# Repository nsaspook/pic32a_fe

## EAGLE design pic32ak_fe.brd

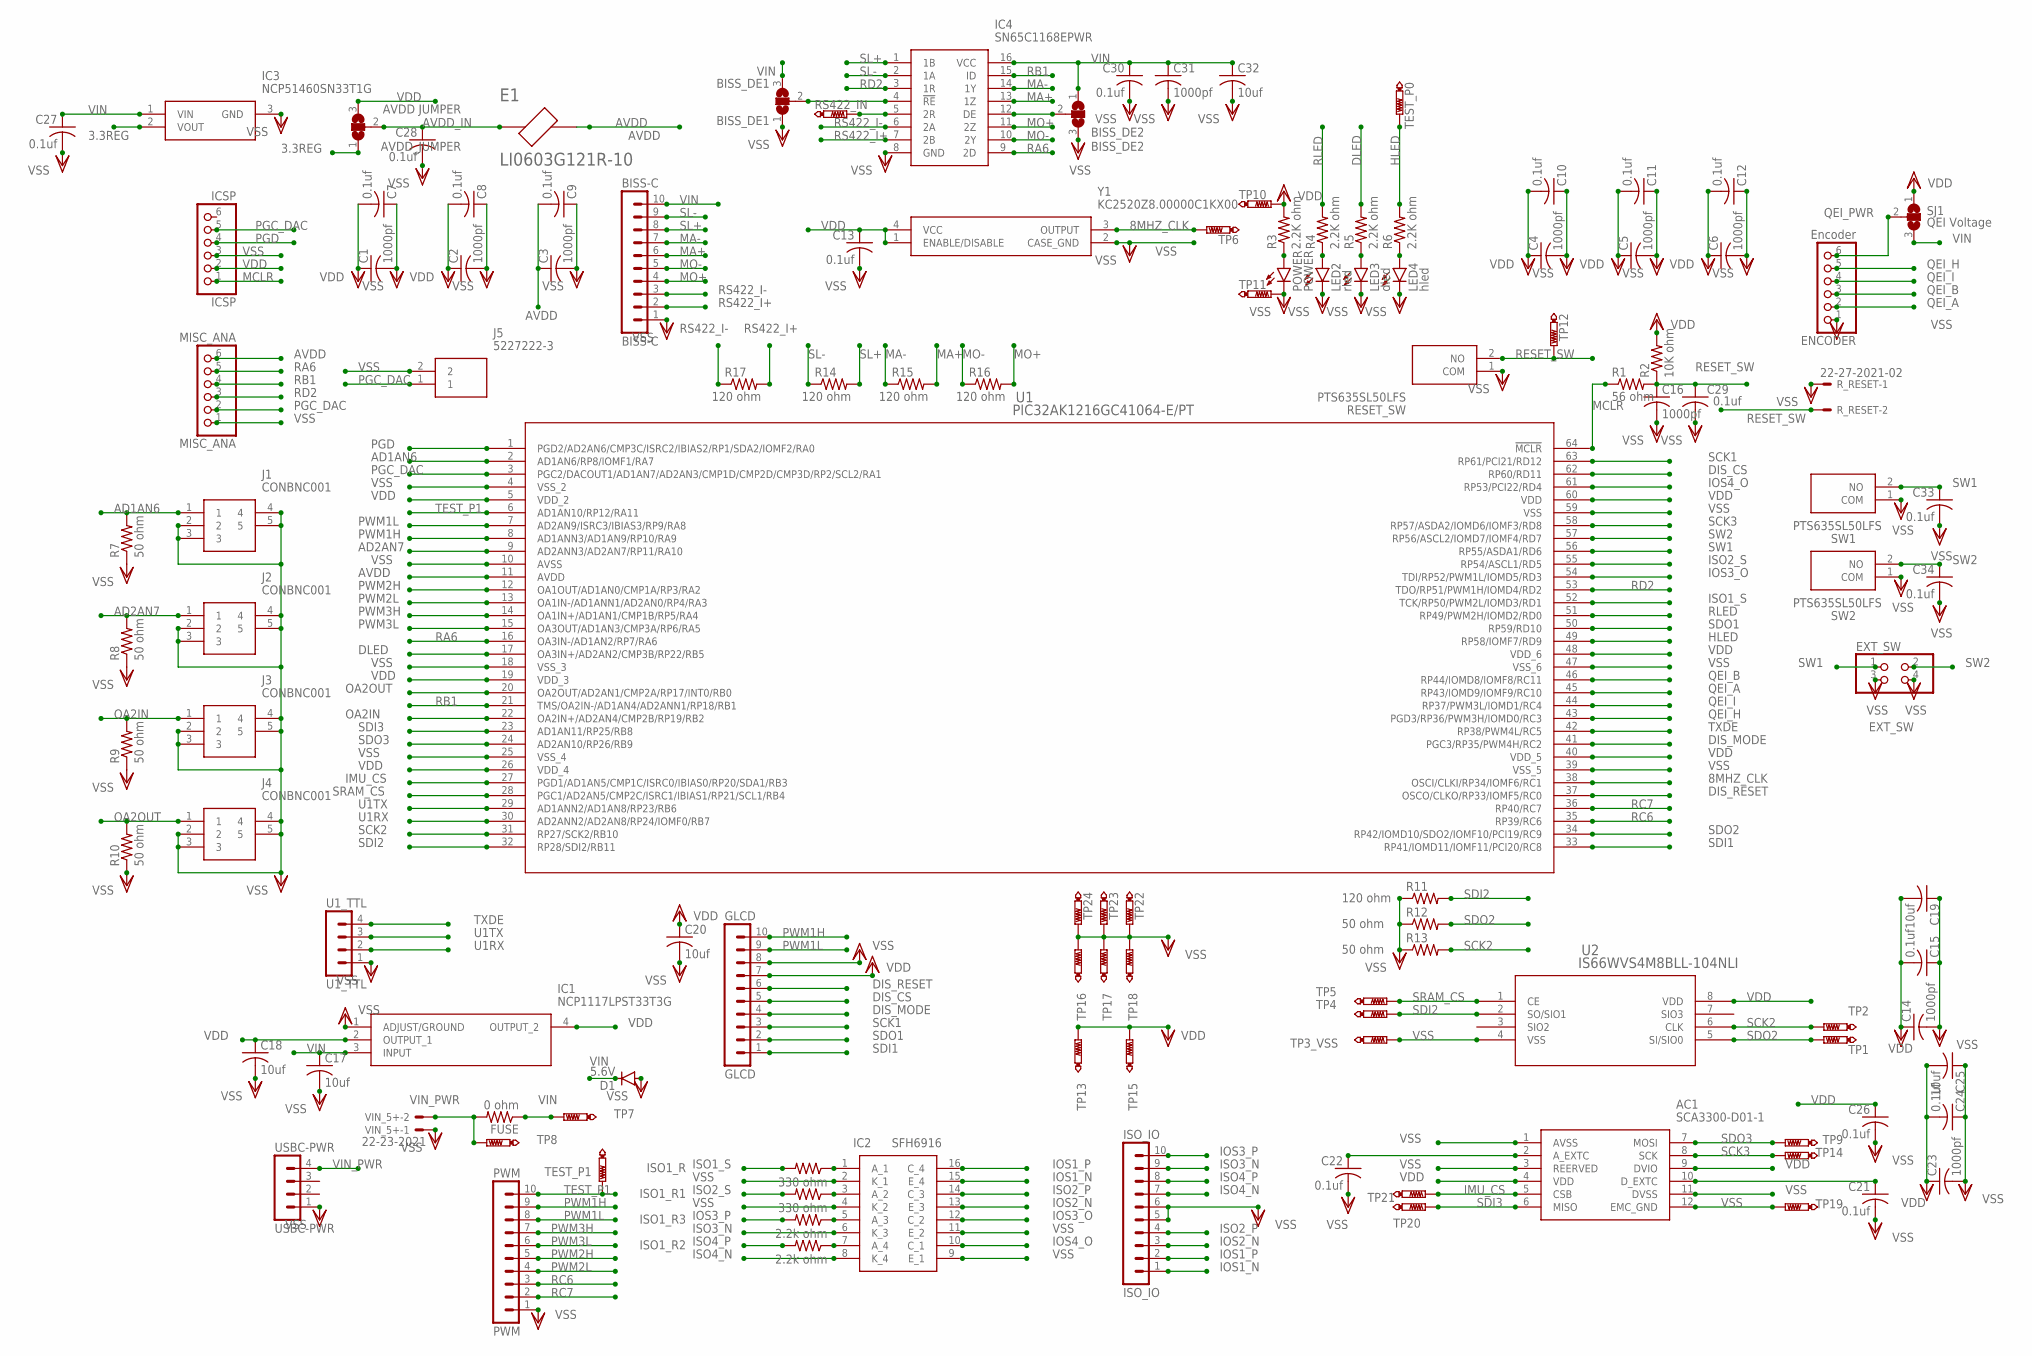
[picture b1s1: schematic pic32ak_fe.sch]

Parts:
AC1: SCA3300-D01-1; SCA3300
AVDD_JUMPER: AVDD JUMPER; SJ_2
BISS-C: BISS-C; MA10-1
BISS_DE1: BISS_DE1; SJ_2
BISS_DE2: BISS_DE2; SJ_2
C1, C2, C3, C4, C5, C6, C14, C16, C23, C31: 1000pf; C0603
C7, C8, C9, C10, C11, C12, C13, C15, C21, C22, C24, C26, C27, C28, C29, C30, C33, C34: 0.1uf; C0603
C17, C18, C19, C20, C25, C32: 10uf; C0805
D1: 5.6V; SMB
E1: LI0603G121R-10; FB_LI0603G121R-10
ENCODER: Encoder; 1X06/90
EXT_SW: EXT_SW; 2X02
FUSE: 0 ohm; R0805
GLCD: GLCD; MA10-1
IC1: NCP1117LPST33T3G; SOT230P700X180-4N
IC2: SFH6916; SOIC127P700X230-16N
IC3: NCP51460SN33T1G; SOT96P237X111-3N
IC4: SN65C1168EPWR; SOP65P640X120-16N
ICSP: ICSP; 1X06/90
ISO1_R, ISO1_R1: 330 ohm; R0805
ISO1_R2, ISO1_R3: 2.2k ohm; R0805
ISO_IO: ISO_IO; MA10-1
J1, J2, J3, J4: CONBNC001
J5: 5227222-3; 52272223
LED2: rled; CHIP-LED0603
LED3: dled; CHIP-LED0603
LED4: hled; CHIP-LED0603
MISC_ANA: MISC_ANA; 1X06/90
POWER: POWER; CHIP-LED0603
PWM: PWM; MA10-1
R1: 56 ohm; R0805
R2: 10K ohm; R0805
R3, R4, R5, R6: 2.2K ohm; R0805
R7, R8, R9, R10: 50 ohm; R0805
R11, R14, R15, R16, R17: 120 ohm; R0603
R12, R13: 50 ohm; R0603
RESET_SW: PTS635SL50LFS
RS422_IN: PTR1PAD1-13; P1-13
R_RESET: 22-27-2021-02; 6410-02
SJ1: QEI Voltage; SJ_2
SW1, SW2: PTS635SL50LFS
TEST_P0, TEST_P1: PTR1PAD1-20; P1-20
TP1, TP2, TP3_VSS, TP4, TP5, TP6, TP7, TP8, TP9, TP13, TP14, TP15, TP16, TP17, TP18, TP19, TP20, TP21, TP22, TP23, TP24: PTR1PAD1-13; P1-13
TP10, TP11, TP12: PTR1PAD1-20; P1-20
U1: PIC32AK1216GC41064-E/PT; TQFP64_PT_MCH
U1_TTL: U1_TTL; MA04-1
U2: IS66WVS4M8BLL-104NLI; SOIC8_150MIL_N_ISI
USBC-PWR: USBC-PWR; MA04-1
VIN_5+: 22-23-2021
Y1: KC2520Z8.00000C1KX00; KC2520Z800000C1KX00

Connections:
3.3REG: AVDD_JUMPER.1, IC3.2 (VOUT)
8MHZ_CLK: TP6.TP, U1.38 (OSCI/CLKI/RP34/IOMF6/RC1), Y1.3 (OUTPUT)
AD1AN6: J1.1, R7.2, U1.2 (AD1AN6/RP8/IOMF1/RA7)
AD2AN7: J2.1, R8.2, U1.9 (AD2ANN3/AD2AN7/RP11/RA10)
AVDD: C3.1, C9.2, E1.2, MISC_ANA.6, U1.11 (AVDD)
AVDD_IN: AVDD_JUMPER.2, C28.1, E1.1
DIS_CS: GLCD.5, U1.62 (RP60/RD11)
DIS_MODE: GLCD.4, U1.41 (PGC3/RP35/PWM4H/RC2)
DIS_RESET: GLCD.6, U1.37 (OSCO/CLKO/RP33/IOMF5/RC0)
DLED: R5.2, U1.17 (OA3IN+/AD2AN2/CMP3B/RP22/RB5)
HLED: R6.2, TEST_P0.TP, U1.49 (RP58/IOMF7/RD9)
IMU_CS: AC1.5 (CSB), TP21.TP, U1.27 (PGD1/AD1AN5/CMP1C/ISRC0/IBIAS0/RP20/SDA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)
IOS1_N: IC2.15 (E_4), ISO_IO.1
IOS1_P: IC2.16 (C_4), ISO_IO.2
IOS2_N: IC2.13 (E_3), ISO_IO.3
IOS3_O: IC2.12 (C_2), U1.54 (TDI/RP52/PWM1L/IOMD5/RD3)
IOS3_P: ISO1_R3.2, ISO_IO.10
IOS4_O: IC2.10 (C_1), U1.61 (RP53/PCI22/RD4)
ISO1_S: ISO1_R.2, U1.52 (TCK/RP50/PWM2L/IOMD3/RD1)
ISO2_P: IC2.14 (C_3), ISO_IO.4
ISO2_S: ISO1_R1.2, U1.55 (RP54/ASCL1/RD5)
ISO3_N: IC2.6 (K_3), ISO_IO.9
ISO4_N: IC2.8 (K_4), ISO_IO.7
ISO4_P: ISO1_R2.2, ISO_IO.8
MA+: BISS-C.6, IC4.13 (1Z), R15.2
MA-: BISS-C.7, IC4.14 (1Y), R15.1
MCLR: ICSP.1, R1.1, U1.64 (!MCLR)
MO+: BISS-C.4, IC4.11 (2Z), R16.2
MO-: BISS-C.5, IC4.10 (2Y), R16.1
unnamed: AC1.2 (A_EXTC), C22.1
unnamed: POWER.A, R3.1
unnamed: LED2.A, R4.1
unnamed: LED3.A, R5.1
unnamed: LED4.A, R6.1
unnamed: AC1.10 (D_EXTC), C21.1
unnamed: IC2.1 (A_1), ISO1_R.1
unnamed: IC2.3 (A_2), ISO1_R1.1
unnamed: IC2.5 (A_3), ISO1_R3.1
unnamed: IC2.7 (A_4), ISO1_R2.1
unnamed: BISS_DE1.2, IC4.4 (!RE)
unnamed: BISS_DE2.2, IC4.12 (DE)
unnamed: IC4.5 (2R), RS422_IN.TP
OA2IN: J3.1, R9.2, U1.22 (OA2IN+/AD2AN4/CMP2B/RP19/RB2)
OA2OUT: J4.1, R10.2, U1.20 (OA2OUT/AD2AN1/CMP2A/RP17/INT0/RB0)
PGC_DAC: ICSP.5, J5.1, MISC_ANA.2, U1.3 (PGC2/DACOUT1/AD1AN7/AD2AN3/CMP1D/CMP2D/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)
PGD: ICSP.4, U1.1 (PGD2/AD2AN6/CMP3C/ISRC2/IBIAS2/RP1/SDA2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)
PWM1H: GLCD.10, PWM.9, U1.8 (AD1ANN3/AD1AN9/RP10/RA9)
PWM1L: GLCD.9, PWM.8, U1.7 (AD2AN9/ISRC3/IBIAS3/RP9/RA8)
PWM2H: PWM.5, U1.12 (OA1OUT/AD1AN0/CMP1A/RP3/RA2)
PWM2L: PWM.4, U1.13 (OA1IN-/AD1ANN1/AD2AN0/RP4/RA3)
PWM3H: PWM.7, U1.14 (OA1IN+/AD1AN1/CMP1B/RP5/RA4)
PWM3L: PWM.6, U1.15 (OA3OUT/AD1AN3/CMP3A/RP6/RA5)
QEI_A: ENCODER.2, U1.45 (RP43/IOMD9/IOMF9/RC10)
QEI_B: ENCODER.3, U1.46 (RP44/IOMD8/IOMF8/RC11)
QEI_H: ENCODER.5, U1.43 (PGD3/RP36/PWM3H/IOMD0/RC3)
QEI_I: ENCODER.4, U1.44 (RP37/PWM3L/IOMD1/RC4)
QEI_PWR: ENCODER.6, SJ1.2
RA6: IC4.9 (2D), MISC_ANA.5, U1.16 (OA3IN-/AD1AN2/RP7/RA6)
RB1: IC4.15 (ID), MISC_ANA.4, U1.21 (TMS/OA2IN-/AD1AN4/AD2ANN1/RP18/RB1)
RC6: PWM.3, U1.35 (RP39/RC6)
RC7: PWM.2, U1.36 (RP40/RC7)
RD2: IC4.3 (1R), MISC_ANA.3, U1.53 (TDO/RP51/PWM1H/IOMD4/RD2)
RESET_SW: C16.1, C29.1, R1.2, R2.1, RESET_SW.2 (NO), R_RESET.2, TP12.TP
RLED: R4.2, U1.51 (RP49/PWM2H/IOMD2/RD0)
RS422_I+: BISS-C.2, IC4.7 (2B), R17.2
RS422_I-: BISS-C.3, IC4.6 (2A), R17.1
SCK1: GLCD.3, U1.63 (RP61/PCI21/RD12)
SCK2: R13.2, TP2.TP, U1.31 (RP27/SCK2/RB10), U2.6 (CLK)
SCK3: AC1.8 (SCK), TP14.TP, U1.58 (RP57/ASDA2/IOMD6/IOMF3/RD8)
SDI1: GLCD.1, U1.33 (RP41/IOMD11/IOMF11/PCI20/RC8)
SDI2: R11.2, TP4.TP, U1.32 (RP28/SDI2/RB11), U2.2 (SO/SIO1)
SDI3: AC1.6 (MISO), TP20.TP, U1.23 (AD1AN11/RP25/RB8)
SDO1: GLCD.2, U1.50 (RP59/RD10)
SDO2: R12.2, TP1.TP, U1.34 (RP42/IOMD10/SDO2/IOMF10/PCI19/RC9), U2.5 (SI/SIO0)
SDO3: AC1.7 (MOSI), TP9.TP, U1.24 (AD2AN10/RP26/RB9)
SL+: BISS-C.8, IC4.1 (1B), R14.2
SL-: BISS-C.9, IC4.2 (1A), R14.1
SRAM_CS: TP5.TP, U1.28 (PGC1/AD2AN5/CMP2C/ISRC1/IBIAS1/RP21/SCL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), U2.1 (CE)
SW1: C33.1, EXT_SW.1, SW1.2 (NO), U1.56 (RP55/ASDA1/RD6)
SW2: C34.1, EXT_SW.2, SW2.2 (NO), U1.57 (RP56/ASCL2/IOMD7/IOMF4/RD7)
TEST_P1: PWM.10, TEST_P1.TP, U1.6 (AD1AN10/RP12/RA11)
TXDE: U1.42 (RP38/PWM4L/RC5), U1_TTL.4
U1RX: U1.30 (AD2ANN2/AD2AN8/RP24/IOMF0/RB7), U1_TTL.2
U1TX: U1.29 (AD1ANN2/AD1AN8/RP23/RB6), U1_TTL.3
VDD: AC1.4 (VDD), AC1.9 (DVIO), AVDD_JUMPER.3, C1.1, C2.1, C4.1, C5.1, C6.1, C7.2, C8.2, C10.2, C11.2, C12.2, C13.1, C14.1, C15.2, C18.1, C19.2, C20.1, C23.1, C24.2, C25.2, C26.1, GLCD.7, IC1.2 (OUTPUT_1), IC1.4 (OUTPUT_2), ICSP.2, R2.2, R3.2, SJ1.1, TP10.TP, TP13.TP, TP15.TP, U1.5 (VDD_2), U1.19 (VDD_3), U1.26 (VDD_4), U1.40 (VDD_5), U1.48 (VDD_6), U1.60 (VDD), U2.8 (VDD), Y1.1 (ENABLE/DISABLE), Y1.4 (VCC)
VIN: BISS-C.10, BISS_DE1.3, BISS_DE2.1, C17.1, C27.1, C30.1, C31.1, C32.1, D1.C, FUSE.1, IC1.3 (INPUT), IC3.1 (VIN), IC4.16 (VCC), SJ1.3, TP7.TP
VIN_PWR: FUSE.2, TP8.TP, USBC-PWR.4, VIN_5+.2
VSS: AC1.1 (AVSS), AC1.3 (REERVED), AC1.11 (DVSS), AC1.12 (EMC_GND), BISS-C.1, BISS_DE1.1, BISS_DE2.3, C1.2, C2.2, C3.2, C4.2, C5.2, C6.2, C7.1, C8.1, C9.1, C10.1, C11.1, C12.1, C13.2, C14.2, C15.1, C16.2, C17.2, C18.2, C19.1, C20.2, C21.2, C22.2, C23.2, C24.1, C25.1, C26.2, C27.2, C28.2, C29.2, C30.2, C31.2, C32.2, C33.2, C34.2, D1.A, ENCODER.1, EXT_SW.3, EXT_SW.4, GLCD.8, IC1.1 (ADJUST/GROUND), IC2.2 (K_1), IC2.4 (K_2), IC2.9 (E_1), IC2.11 (E_2), IC3.3 (GND), IC4.8 (GND), ICSP.3, ISO_IO.5, ISO_IO.6, J1.2, J1.3, J1.4, J1.5, J2.2, J2.3, J2.4, J2.5, J3.2, J3.3, J3.4, J3.5, J4.2, J4.3, J4.4, J4.5, J5.2, LED2.C, LED3.C, LED4.C, MISC_ANA.1, POWER.C, PWM.1, R7.1, R8.1, R9.1, R10.1, R11.1, R12.1, R13.1, RESET_SW.1 (COM), R_RESET.1, SW1.1 (COM), SW2.1 (COM), TP3_VSS.TP, TP11.TP, TP16.TP, TP17.TP, TP18.TP, TP19.TP, TP22.TP, TP23.TP, TP24.TP, U1.4 (VSS_2), U1.10 (AVSS), U1.18 (VSS_3), U1.25 (VSS_4), U1.39 (VSS_5), U1.47 (VSS_6), U1.59 (VSS), U1_TTL.1, U2.4 (VSS), USBC-PWR.1, VIN_5+.1, Y1.2 (CASE_GND)

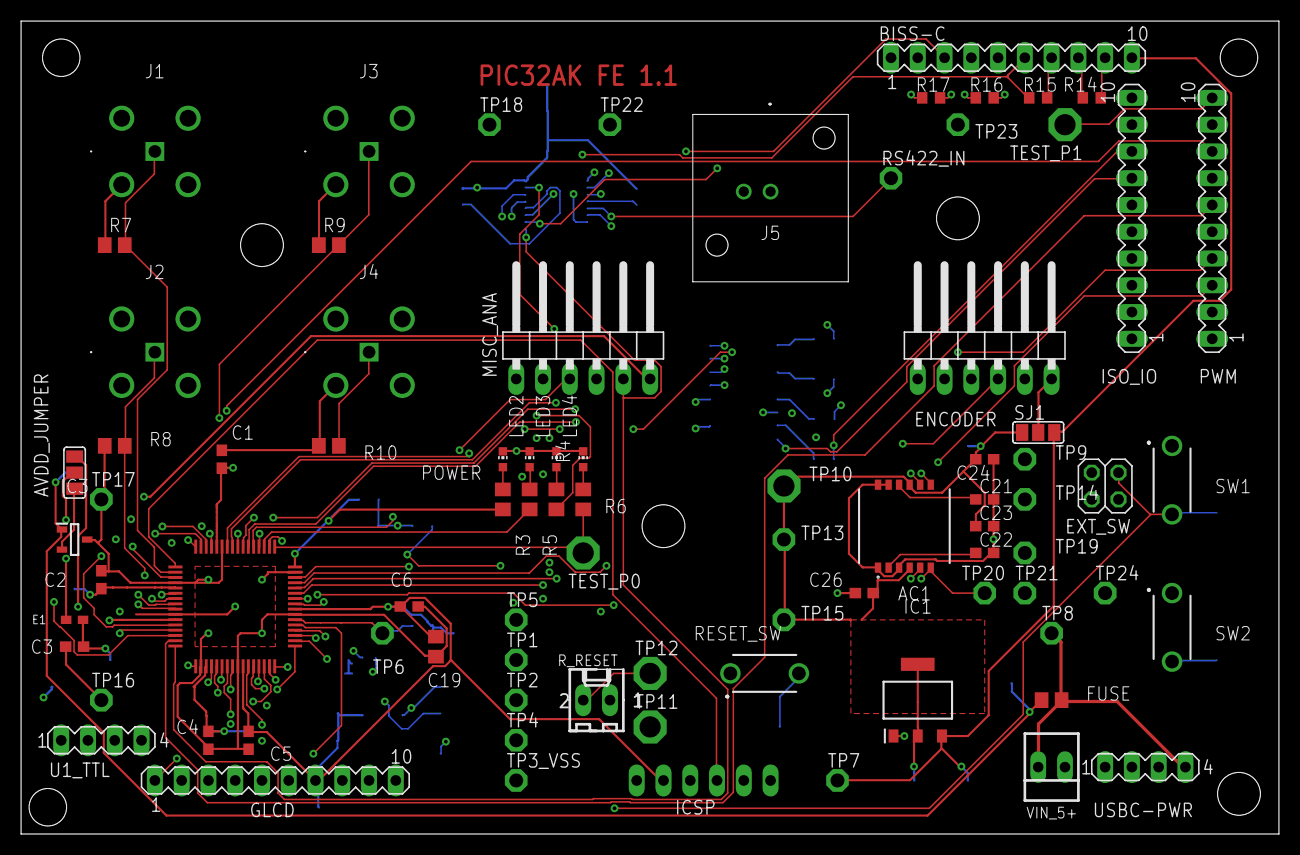
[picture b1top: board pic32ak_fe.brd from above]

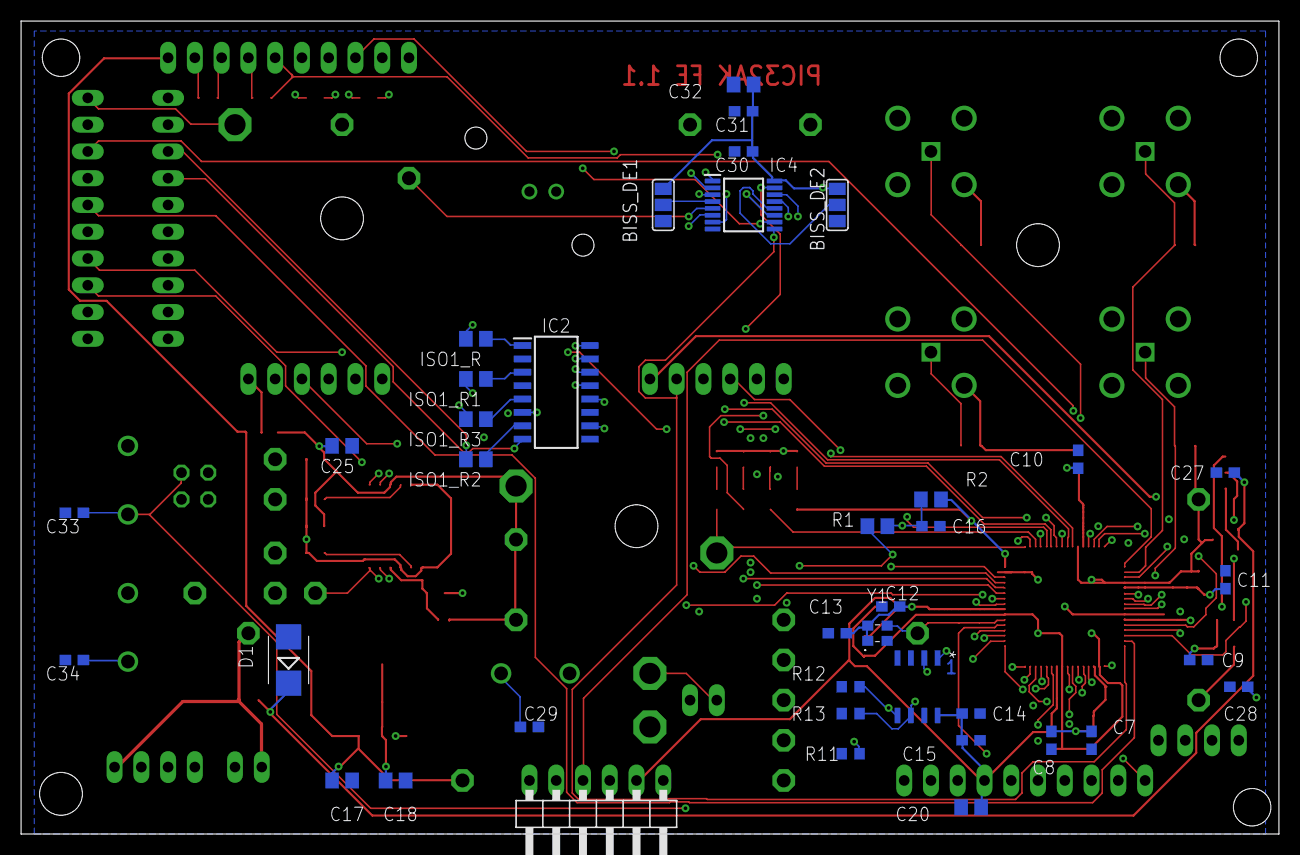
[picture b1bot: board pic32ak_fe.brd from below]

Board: 4 copper layers, 119.4 x 77.1 mm, 121 parts (39 on the bottom side), 88 nets.

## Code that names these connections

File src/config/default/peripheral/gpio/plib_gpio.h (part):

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#define TEST_TP1_Get()               ((PORTA >> 11) & 0x1)
#define TEST_TP1_PIN                 GPIO_PIN_RA11

/*** Macros for DLED pin ***/
#define DLED_Set()               (_LATB5 = 1U)
#define DLED_Clear()             (_LATB5 = 0U)
#define DLED_Toggle()            (_LATB5 ^= 1U)
#define DLED_OutputEnable()      (_TRISB5 = 0U)
#define DLED_InputEnable()       (_TRISB5 = 1U)
#define DLED_Get()               ((PORTB >> 5) & 0x1)
#define DLED_PIN                 GPIO_PIN_RB5

/*** Macros for IMU_CS pin ***/
#define IMU_CS_Set()               (_LATB3 = 1U)
#define IMU_CS_Clear()             (_LATB3 = 0U)
#define IMU_CS_Toggle()            (_LATB3 ^= 1U)
#define IMU_CS_OutputEnable()      (_TRISB3 = 0U)
#define IMU_CS_InputEnable()       (_TRISB3 = 1U)
#define IMU_CS_Get()               ((PORTB >> 3) & 0x1)
#define IMU_CS_PIN                 GPIO_PIN_RB3

/*** Macros for SRAM_CS pin ***/
#define SRAM_CS_Set()               (_LATB4 = 1U)
#define SRAM_CS_Clear()             (_LATB4 = 0U)
#define SRAM_CS_Toggle()            (_LATB4 ^= 1U)
#define SRAM_CS_OutputEnable()      (_TRISB4 = 0U)
#define SRAM_CS_InputEnable()       (_TRISB4 = 1U)
#define SRAM_CS_Get()               ((PORTB >> 4) & 0x1)
#define SRAM_CS_PIN                 GPIO_PIN_RB4

/*** Macros for GPIO_RC6 pin ***/
#define GPIO_RC6_Set()               (_LATC6 = 1U)
#define GPIO_RC6_Clear()             (_LATC6 = 0U)
#define GPIO_RC6_Toggle()            (_LATC6 ^= 1U)
#define GPIO_RC6_OutputEnable()      (_TRISC6 = 0U)
#define GPIO_RC6_InputEnable()       (_TRISC6 = 1U)
#define GPIO_RC6_Get()               ((PORTC >> 6) & 0x1)
#define GPIO_RC6_PIN                 GPIO_PIN_RC6

/*** Macros for GPIO_RC7 pin ***/
#define GPIO_RC7_Set()               (_LATC7 = 1U)
#define GPIO_RC7_Clear()             (_LATC7 = 0U)
#define GPIO_RC7_Toggle()            (_LATC7 ^= 1U)
#define GPIO_RC7_OutputEnable()      (_TRISC7 = 0U)
#define GPIO_RC7_InputEnable()       (_TRISC7 = 1U)
#define GPIO_RC7_Get()               ((PORTC >> 7) & 0x1)
#define GPIO_RC7_PIN                 GPIO_PIN_RC7

/*** Macros for DIS_RESET pin ***/
#define DIS_RESET_Set()               (_LATC0 = 1U)
#define DIS_RESET_Clear()             (_LATC0 = 0U)
#define DIS_RESET_Toggle()            (_LATC0 ^= 1U)
#define DIS_RESET_OutputEnable()      (_TRISC0 = 0U)
#define DIS_RESET_InputEnable()       (_TRISC0 = 1U)
#define DIS_RESET_Get()               ((PORTC >> 0) & 0x1)
#define DIS_RESET_PIN                 GPIO_PIN_RC0

/*** Macros for DIS_MODE pin ***/
#define DIS_MODE_Set()               (_LATC2 = 1U)
#define DIS_MODE_Clear()             (_LATC2 = 0U)
#define DIS_MODE_Toggle()            (_LATC2 ^= 1U)
#define DIS_MODE_OutputEnable()      (_TRISC2 = 0U)
#define DIS_MODE_InputEnable()       (_TRISC2 = 1U)
#define DIS_MODE_Get()               ((PORTC >> 2) & 0x1)
#define DIS_MODE_PIN                 GPIO_PIN_RC2

/*** Macros for TXDE pin ***/
#define TXDE_Set()               (_LATC5 = 1U)
#define TXDE_Clear()             (_LATC5 = 0U)
#define TXDE_Toggle()            (_LATC5 ^= 1U)
#define TXDE_OutputEnable()      (_TRISC5 = 0U)
#define TXDE_InputEnable()       (_TRISC5 = 1U)
#define TXDE_Get()               ((PORTC >> 5) & 0x1)
#define TXDE_PIN                 GPIO_PIN_RC5

/*** Macros for TEST_TP0 pin ***/
#define TEST_TP0_Set()               (_LATD9 = 1U)
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#define TEST_TP0_Get()               ((PORTD >> 9) & 0x1)
#define TEST_TP0_PIN                 GPIO_PIN_RD9

/*** Macros for RLED pin ***/
#define RLED_Set()               (_LATD0 = 1U)
#define RLED_Clear()             (_LATD0 = 0U)
#define RLED_Toggle()            (_LATD0 ^= 1U)
#define RLED_OutputEnable()      (_TRISD0 = 0U)
#define RLED_InputEnable()       (_TRISD0 = 1U)
#define RLED_Get()               ((PORTD >> 0) & 0x1)
#define RLED_PIN                 GPIO_PIN_RD0

/*** Macros for ISO1_S pin ***/
#define ISO1_S_Set()               (_LATD1 = 1U)
#define ISO1_S_Clear()             (_LATD1 = 0U)
#define ISO1_S_Toggle()            (_LATD1 ^= 1U)
#define ISO1_S_OutputEnable()      (_TRISD1 = 0U)
#define ISO1_S_InputEnable()       (_TRISD1 = 1U)
#define ISO1_S_Get()               ((PORTD >> 1) & 0x1)
#define ISO1_S_PIN                 GPIO_PIN_RD1

/*** Macros for ISO3_O pin ***/
#define ISO3_O_Set()               (_LATD3 = 1U)
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#define ISO3_O_Get()               ((PORTD >> 3) & 0x1)
#define ISO3_O_PIN                 GPIO_PIN_RD3

/*** Macros for ISO2_S pin ***/
#define ISO2_S_Set()               (_LATD5 = 1U)
#define ISO2_S_Clear()             (_LATD5 = 0U)
#define ISO2_S_Toggle()            (_LATD5 ^= 1U)
#define ISO2_S_OutputEnable()      (_TRISD5 = 0U)
#define ISO2_S_InputEnable()       (_TRISD5 = 1U)
#define ISO2_S_Get()               ((PORTD >> 5) & 0x1)
#define ISO2_S_PIN                 GPIO_PIN_RD5

/*** Macros for SW1 pin ***/
#define SW1_Set()               (_LATD6 = 1U)
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#define ISO4_O_Get()               ((PORTD >> 4) & 0x1)
#define ISO4_O_PIN                 GPIO_PIN_RD4

/*** Macros for DIS_CS pin ***/
#define DIS_CS_Set()               (_LATD11 = 1U)
#define DIS_CS_Clear()             (_LATD11 = 0U)
#define DIS_CS_Toggle()            (_LATD11 ^= 1U)
#define DIS_CS_OutputEnable()      (_TRISD11 = 0U)
#define DIS_CS_InputEnable()       (_TRISD11 = 1U)
#define DIS_CS_Get()               ((PORTD >> 11) & 0x1)
#define DIS_CS_PIN                 GPIO_PIN_RD11
    
#define   GPIO_PORT_A (0U)
#define   GPIO_PORT_B (1U)
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
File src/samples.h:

/*
 * File:   samples.h
 * Author: root
 *
 * Created on November 10, 2025, 12:16 PM
 */

#ifndef SAMPLES_H
#define	SAMPLES_H

#ifdef	__cplusplus
extern "C" {
#endif
#include <xc.h>
#include <stddef.h>                     // Defines NULL
#include <stdbool.h>                    // Defines true
#include <stdlib.h>                     // Defines EXIT_FAILURE
#include <ctype.h>
#include <stdio.h>
#include <string.h>
#include "definitions.h"                // SYS function prototypes

#define FE_DRIVER "V1.06"
#define FE_ALIAS "PIC32AK FE"

	//#define ISS_DMA_READ

#define SCA3300
#define IMU_ID		3

#define IMU_BUF		256
#define FFT_BUF		64
#define SAMPLE_BUF	32
#define SAMPLE_TIMEOUT	2

#define NUM_ADC	2
#define ADC1_D	0
#define ADC2_D	1
#define ADC_SAMC	1

#define ADC1_SCALE	0.000418000f
#define ADC2_SCALE	0.000412000f

#define DAC1_CAL	1275

#define DIS_TICKS	100
#define IMU_TICKS	1
#define GFX_TICKS	30000

	/*
	 * isolated DIO pins
	 */
#define ISOO3_PORT_G		ISO3_O_Get()
#define ISOO4_PORT_G		ISO4_O_Get()

#define ISOI1_LAT_S		ISO1_S_Set()
#define ISOI1_LAT_C		ISO1_S_Clear()
#define ISOI1_LAT_L		ISO1_S_Get()

#define ISOI2_LAT_S		ISO2_S_Set()
#define ISOI2_LAT_C		ISO2_S_Clear()
#define ISOI2_LAT_L		ISO2_S_Get()

#define RETRIGGER_TIME	150

	static const uint32_t MAX_ISS66_SAMPLES = 256; // sram ADC samples to write, X4 bytes
	static const uint32_t MAX_ISS66_PAGES_8MBIT = 512; // sram pages to write
	static const uint32_t MAX_ISS66_PAGES_16MBIT = 512;
	static const uint32_t MAX_ISS66_PAGES_32MBIT = 512;
	static const uint32_t ISS66_PAGE_SIZE = 1024;
	static const size_t SRAM_READ_SAMPLES = 25;
	static const uint32_t ISS_FAST_CMD_SIZE = 5;
	static const uint32_t ISS_WRITE_CMD_SIZE = 4;
	static const uint32_t ADC_SAMPLES_SIZE = 4;
	static const uint32_t ADC_SAMPLES_START = 4;
	/*
	 * unconfigured pins RA6, RC6, RC7, RD2, RB1
	 * RA11 = TP1
	 * RB1 BISS1 MA, OUTPUT
	 * RD2 BISS1 SL, INPUT
	 * RA6 BISS1 MO, OUTPUT
	 */

	extern bool SW1_SET, SW2_SET;
	extern double adc1_scaled, adc2_scaled;

	enum iss_sample_type {
		ISS_INIT = 0, // ISS FSM states
		ISS_PAGE,
		ISS_STORE,
		ISS_NULL,
		ISS_LAST,
	};

	enum iss_chip_type {
		ISS_ISS_UNK = 0, // ISS chip models, UNK means chip read error
		ISS_ISS_8Mb,
		ISS_ISS_16Mb,
		ISS_ISS_32Mb,
		ISS_ISS_BAD, // unknown id
		ISS_ISS_LAST,
	};

	void fe_version(void);
	/*
	 * PIC32AK FE board firmware
	 * V1.00	Alpha testing versions
	 * V1.01	add iso DIO, set SPI2 speeds to max
	 * V1.02	code cleanups
	 * V1.03	SRAM chip ID setups
	 * V1.04	DISABLE JTAG so pins D[1--3], RB1 will work
	 * V1.05	SRAM chip error detection fixes
	 */

#ifdef	__cplusplus
}
#endif

#endif	/* SAMPLES_H */

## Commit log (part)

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2025-11-04 project start
2025-11-09 timer triggered version
2025-11-17 all pins conneced on PCB
2025-11-29 ADC updates
2025-11-30 dual ADC conversions
2025-12-01 add cude display JAVA code
2025-12-05 max SPI2 speed
2025-12-09 full sram page storage
2025-12-12 speed tweak
2025-12-15 finish V1.1 board
2025-12-20 up PCB
2026-01-20 update to PTG triggers
2026-01-21 doxygen

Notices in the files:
src/config/default/peripheral/gpio/plib_gpio.h:
Copyright (C) 2025 Microchip Technology Inc. and its subsidiaries.
parts and their libraries:
COPYRIGHT: Copyright (C) 2025 Ultra Librarian. All rights reserved.
